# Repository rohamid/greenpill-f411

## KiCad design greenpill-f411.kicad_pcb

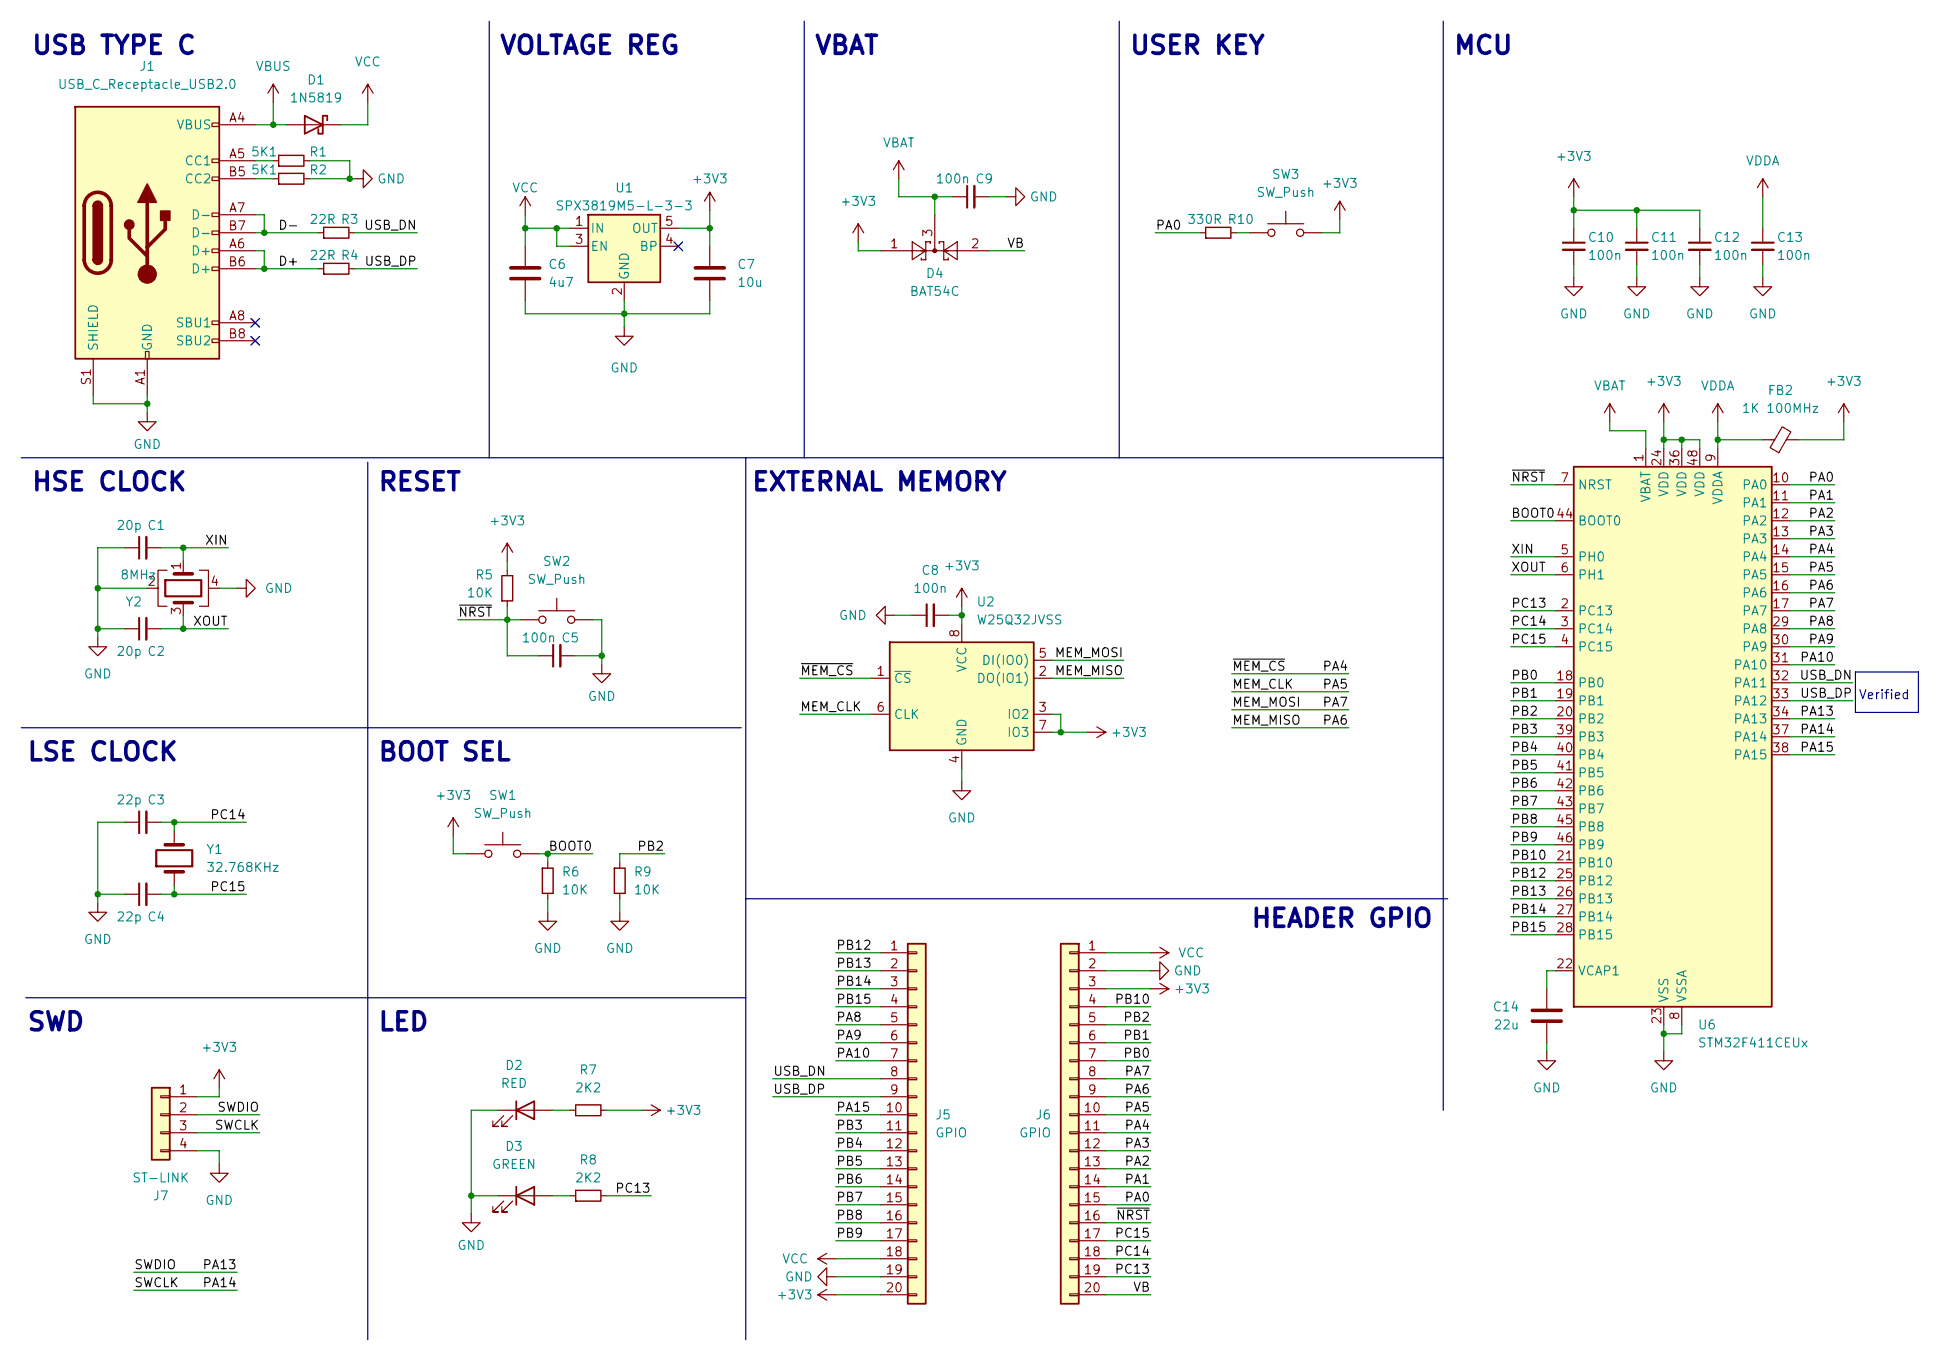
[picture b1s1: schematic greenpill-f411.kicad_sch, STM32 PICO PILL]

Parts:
C1, C2: 20p; C_0402_1005Metric; LCSC Part Number C1554
C3, C4: 22p; C_0402_1005Metric; LCSC Part Number C1555
C5, C8, C9, C10, C11, C12, C13: 100n; C_0402_1005Metric; LCSC Part Number C307331
C6: 4u7; C_0603_1608Metric; LCSC Part Number C19666
C7: 10u; C_0603_1608Metric; LCSC Part Number C19702
C14: 22u; C_0603_1608Metric; LCSC Part Number C19702
D1: 1N5819; D_SOD-323; LCSC Part Number C191023
D2: RED; LED_0805_2012Metric; LCSC Part Number C84256
D3: GREEN; LED_0805_2012Metric; LCSC Part Number C34499
D4: BAT54C; SOT-23; LCSC Part Number C37704
FB2: 1K 100MHz; L_0402_1005Metric; LCSC Part Number C76884
J1: USB_C_Receptacle_USB2.0; USB_C_Receptacle_G-Switch_GT-USB-7010ASV; LCSC Part Number C963413
J5, J6: GPIO; PinHeader_1x20_P2.54mm_Vertical
J7: ST-LINK; PinHeader_1x04_P2.54mm_Vertical
R1, R2: 5K1; R_0402_1005Metric; LCSC Part Number C25905
R3, R4: 22R; R_0402_1005Metric; LCSC Part Number C25092
R5, R6, R9: 10K; R_0402_1005Metric; LCSC Part Number C25744
R7, R8: 2K2; R_0402_1005Metric; LCSC Part Number C25879
R10: 330R; R_0402_1005Metric; LCSC Part Number C25104
SW1, SW2, SW3: SW_Push; SW_Push_1P1T_NO_CK_KMR2; LCSC Part Number C127488
U1: SPX3819M5-L-3-3; SOT-23-5; LCSC Part Number C9055
U2: W25Q32JVSS; SOIC-8_5.23x5.23mm_P1.27mm
U6: STM32F411CEUx; QFN-48-1EP_7x7mm_P0.5mm_EP5.6x5.6mm
Y1: 32.768KHz; Crystal_SMD_3215-2Pin_3.2x1.5mm; LCSC Part Number C93232
Y2: 8MHz; Crystal_SMD_3225-4Pin_3.2x2.5mm; LCSC Part Number C253723

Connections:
+3V3: C7.1, C8.2, C10.1, C11.1, C12.1, D4.1, FB2.2, J5.20, J6.3, J7.1, R5.2, R7.2, SW1.1, SW3.2, U1.5 (OUT), U2.3 (IO2), U2.7 (IO3), U2.8 (VCC), U6.24 (VDD), U6.36 (VDD), U6.48 (VDD)
/BOOT0: R6.1, SW1.2, U6.44 (BOOT0)
/D+: J1.A6 (D+), J1.B6 (D+), R4.1
/D-: J1.A7 (D-), J1.B7 (D-), R3.1
/MEM_CLK: J6.10, U2.6 (CLK), U6.15 (PA5)
/MEM_MISO: J6.9, U2.2 (DO(IO1)), U6.16 (PA6)
/MEM_MOSI: J6.8, U2.5 (DI(IO0)), U6.17 (PA7)
/PA0: J6.15, R10.1, U6.10 (PA0)
/PA1: J6.14, U6.11 (PA1)
/PA2: J6.13, U6.12 (PA2)
/PA3: J6.12, U6.13 (PA3)
/PA4: J6.11, U2.1 (~CS), U6.14 (PA4)
/PA8: J5.5, U6.29 (PA8)
/PA9: J5.6, U6.30 (PA9)
/PA10: J5.7, U6.31 (PA10)
/PA13: J7.2, U6.34 (PA13)
/PA14: J7.3, U6.37 (PA14)
/PA15: J5.10, U6.38 (PA15)
/PB0: J6.7, U6.18 (PB0)
/PB1: J6.6, U6.19 (PB1)
/PB2: J6.5, R9.1, U6.20 (PB2)
/PB3: J5.11, U6.39 (PB3)
/PB4: J5.12, U6.40 (PB4)
/PB5: J5.13, U6.41 (PB5)
/PB6: J5.14, U6.42 (PB6)
/PB7: J5.15, U6.43 (PB7)
/PB8: J5.16, U6.45 (PB8)
/PB9: J5.17, U6.46 (PB9)
/PB10: J6.4, U6.21 (PB10)
/PB12: J5.1, U6.25 (PB12)
/PB13: J5.2, U6.26 (PB13)
/PB14: J5.3, U6.27 (PB14)
/PB15: J5.4, U6.28 (PB15)
/PC13: J6.19, R8.2, U6.2 (PC13)
/PC14: C3.2, J6.18, U6.3 (PC14), Y1.2
/PC15: C4.2, J6.17, U6.4 (PC15), Y1.1
/USB_DN: J5.8, R3.2, U6.32 (PA11)
/USB_DP: J5.9, R4.2, U6.33 (PA12)
/VB: D4.2, J6.20
/XIN: C1.2, U6.5 (PH0), Y2.1
/XOUT: C2.2, U6.6 (PH1), Y2.3
/~NRST: C5.1, J6.16, R5.1, SW2.1, U6.7 (NRST)
GND: C1.1, C2.1, C3.1, C4.1, C5.2, C6.2, C7.2, C8.1, C9.2, C10.2, C11.2, C12.2, C13.2, C14.2, D2.1 (K), D3.1 (K), J1.A1 (GND), J1.A12 (GND), J1.B1 (GND), J1.B12 (GND), J1.S1 (SHIELD), J5.19, J6.2, J7.4, R1.2, R2.2, R6.2, R9.2, SW2.2, U1.2 (GND), U2.4 (GND), U6.8 (VSSA), U6.23 (VSS), U6.35 (VSS), U6.47 (VSS), U6.49 (VSS), Y2.2, Y2.4
unnamed: D2.2 (A), R7.1
unnamed: D3.2 (A), R8.1
unnamed: J1.A5 (CC1), R1.1
unnamed: J1.B5 (CC2), R2.1
unnamed: R10.2, SW3.1
unnamed: C14.1, U6.22 (VCAP1)
VBAT: C9.1, D4.3, U6.1 (VBAT)
VBUS: D1.2 (A), J1.A4 (VBUS), J1.A9 (VBUS), J1.B4 (VBUS), J1.B9 (VBUS)
VCC: C6.1, D1.1 (K), J5.18, J6.1, U1.1 (IN), U1.3 (EN)
VDDA: C13.1, FB2.1, U6.9 (VDDA)

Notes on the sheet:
MCU
RESET
BOOT SEL
HEADER GPIO
EXTERNAL MEMORY
VOLTAGE REG
Verified
VBAT
SWD
USB TYPE C
LED
HSE CLOCK
USER KEY
LSE CLOCK

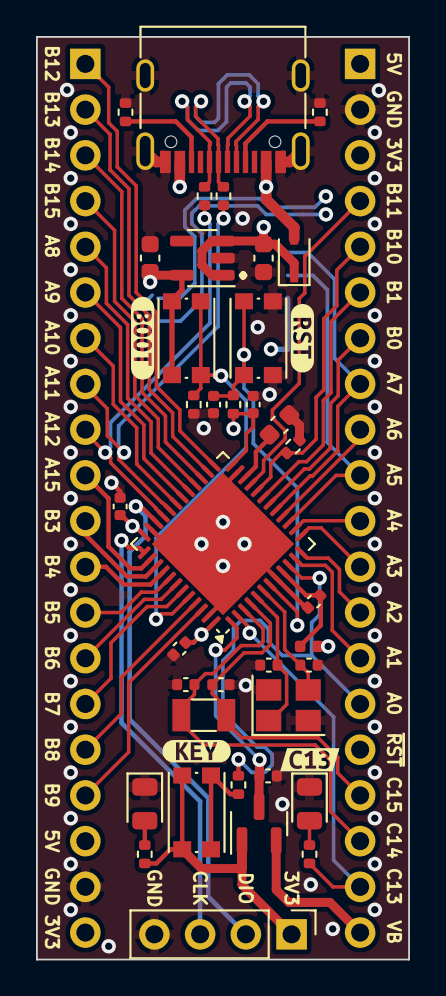
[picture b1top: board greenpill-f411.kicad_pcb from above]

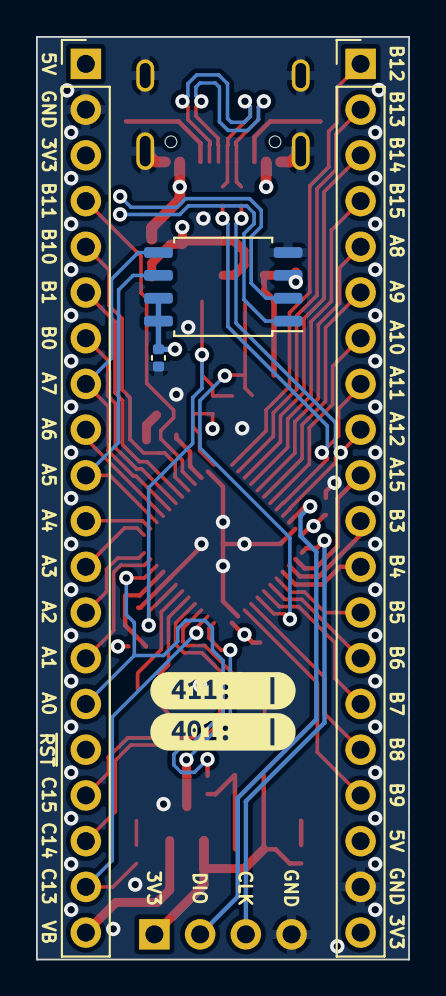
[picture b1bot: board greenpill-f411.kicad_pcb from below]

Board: 4 copper layers, 20.7 x 51.3 mm, 47 parts (6 on the bottom side), 53 nets.

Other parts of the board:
kibuzzard-63FDC3E6: G***; kibuzzard-63FDC3E6
kibuzzard-63FDC36C: G***; kibuzzard-63FDC36C
kibuzzard-63FDC37C: G***; kibuzzard-63FDC37C
kibuzzard-63FDCD3E: G***; kibuzzard-63FDCD3E
kibuzzard-663AE55A: G***; kibuzzard-663AE55A
kibuzzard-663AE56E: G***; kibuzzard-663AE56E

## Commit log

2024-05-13 Finished
